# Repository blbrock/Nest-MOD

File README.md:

# Nest-MOD
Nest-MOD is a hardware and software interface to allow Nest Thermostats to work more efficiently with high efficiency
modulating/condensing boilers and furnaces that incorporate outdoor reset.

Requires python_nest API developed by Jason Kölker:
https://github.com/jkoelker/python-nest/

# Background
Modulating/Condensing (mod/con) boilers with Outdoor Reset (ODR) function are among the most energy 
efficient home heating devices available. However, because mod/con boilers operate at lower output 
temperatures than conventional boilers and furnaces, they do not work well with advanced programable 
and learning thermostats (e.g. Nest) that offer energy savings by programming nightly temperature 
setbacks or when homes are not occupied. Mod/con boilers with ODR adjust their heat output to compensate 
for outdoor temperatures by dialing back heat ouput during warm weather and increasing output when it is 
cold. A properly tuned mod/con ODR boiler will produce just enough heat to compensate for the building's 
heat loss and therefore run at lower temperatures for periods of time compared to a conventional system.

Because of their lower operating temperatures, mod/con ODR boilers can take many hours to recover from a 
temperature setback, if they recover at all. This is particularly true for radiant floor heating systems 
which are great for maintaining temperatures, but respond slowly to thermostat changes. 
Some boilers include a boost function that increases boiler output to speed recovery from temperature 
setbacks but many do not. 

Using temperature setbacks with radiant floor heating, and particularly with mod/con boilers, is a 
controversial topic. However, a study conducted by the National Renewable Energy Laboratory (NREL) 
indicates that nightly temperature setbacks do save energy in radiant floor, mod/con systems even if the 
boiler has to work harder to recover from those setbacks (http://www.nrel.gov/docs/fy14osti/60200.pdf).

Most networked thermostats do not include support for ODR furnaces and boilers. Nest 3rd 
generation thermostats sold in European markets now provides support for OpenTherm compliant modulating 
boilers which allows the thermostat to communicate with the boiler but currently cannot control boiler 
temperature. Based on discussions with Nest support, there doesn't appear to be any plan to implement 
modulating boiler support of any kind in the US. Therefore, one of the main energy saving advantages of 
programable thermostats is lost on systems that cannot recover from temperature setbacks in a reasonable 
time.

Frustrated by the lack of support for modulating boilers, I decided to build my own interface shield for 
a Raspberry pi. The shield and software are designed for a Munchkin boiler but should work (with appropriate 
modifcation) on any boiler that uses a thermistor to control the ODR curve. 

# Features: 

The software monitors thermostat data and initiates an ODR override cycle when > 1.25F temperature increase 
is called by any thermostat. Three stages of boost are provided depending on the differential between room 
ambient temperature and the target temperature the thermostat is trying to reach. Boost stage (and boiler 
temperature) increases with increasing differentials. Temperature differental threshold for each boost stage 
can be adjusted in the configuration (.secrets) file. Once the differential between target and room temperature 
reaches < 0.25F, ODR override is canceled and the boiler returns to its default ODR state.

The software tracks all thermostats in a Nest account and adjusts boost stages upward or downward according to 
the maximum boost level being requested by all thermostats in the account.

# Extras:

1. boost.py - a simple command line program to provide manual boost if needed. Manual boost cycles are logged (see below).

2. Automatic dehumidifier adjustment:
The software contains an optional routine to adjust the humidity setting for a selected thermostat according 
to outside temperature. This is useful for controlling an HRV or dehumidifier to maintain optimal indoor
humidity in cold climates. This feature does not require the pi to function.

3. Data logging:
Data from nest thermostats may optionally be logged to a file by setting options in the .secrets configuration file. 
This produces a comma delimited file containing data from thermostats and boost conditions. his feature does not require the pi to function.

4. Data Graphing:
When executed, plot_nest.py will produce a graph of data for the past week for all thermostats.  This program has only been tested in a Windows PC environment and may need additional software, configuration, or modifiction to work on other platforms.

# Error checking and logging: 

ODR override events and communication failures are logged to nest_odr.log. If the device loses connection with
the Nest server during an ODR override cycle, it will continue to recheck the connection at 1 minute intervals 
for 30 minutes. If a connection is not made within 30 minutes, the ODR override is aborted and the boiler is 
returned to its default state.

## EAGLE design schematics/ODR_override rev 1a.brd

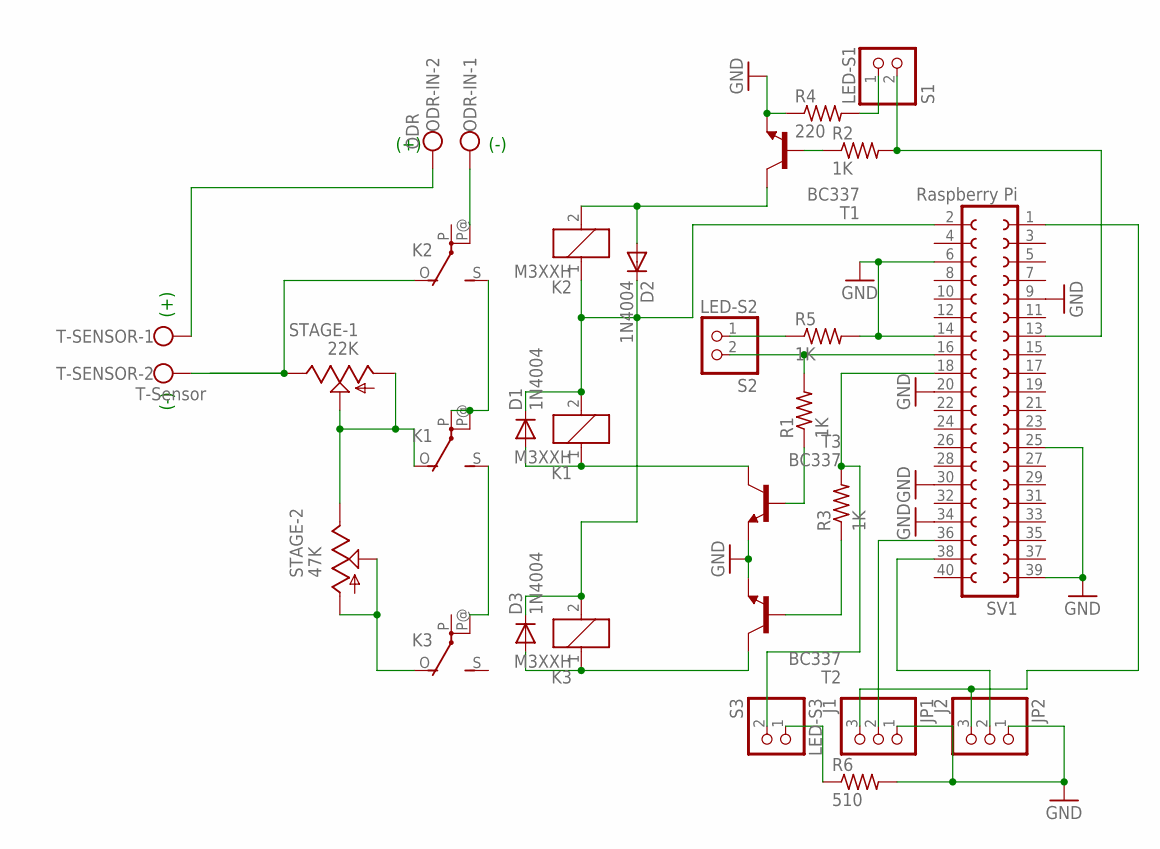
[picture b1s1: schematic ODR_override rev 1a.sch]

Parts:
D1, D2, D3: 1N4004; DO41-10
JP1: J1; 1X03
JP2: J2; 1X03
K1, K2, K3: M3XXH
LED-S1: S1; 1X02
LED-S2: S2; 1X02
LED-S3: S3; 1X02
ODR-IN: ODR; W237-102
R1, R2, R3, R5: 1K; 0204/7
R4: 220; 0204/7
R6: 510; 0204/7
STAGE-1: 22K; B25P
STAGE-2: 47K; B25P
SV1: Raspberry Pi; FE20-2
T1, T2, T3: BC337; TO92
T-SENSOR: T-Sensor; W237-102

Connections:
GND: JP1.1, JP2.1, R4.1, R5.2, R6.2, SV1.6, SV1.9, SV1.14, SV1.20, SV1.25, SV1.30, SV1.34, SV1.39, T1.1 (E), T2.1 (E), T3.1 (E)
unnamed: D1.A, K1.1, T3.3 (C)
unnamed: LED-S1.2, R2.2, SV1.13
unnamed: K1.S, K3.P@
unnamed: K2.P@, ODR-IN.1
unnamed: LED-S3.2, R3.2, SV1.18
unnamed: D3.A, K3.1, T2.3 (C)
unnamed: ODR-IN.2, T-SENSOR.1
unnamed: K1.O, STAGE-1.A, STAGE-1.S, STAGE-2.E
unnamed: D2.A, K2.2, T1.3 (C)
unnamed: R2.1, T1.2 (B)
unnamed: JP1.3, JP2.3, SV1.1
unnamed: LED-S2.2, R1.2, SV1.16
unnamed: R3.1, T2.2 (B)
unnamed: R1.1, T3.2 (B)
unnamed: K2.O, STAGE-1.E, T-SENSOR.2
unnamed: K1.P, K1.P@, K2.S
unnamed: K3.O, STAGE-2.A, STAGE-2.S
unnamed: JP1.2, SV1.36
unnamed: JP2.2, SV1.38
unnamed: LED-S1.1, R4.2
unnamed: LED-S2.1, R5.1
unnamed: LED-S3.1, R6.1
VCC: D1.C, D2.C, D3.C, K1.2, K2.1, K3.2, SV1.2

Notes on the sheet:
(+)
(-)

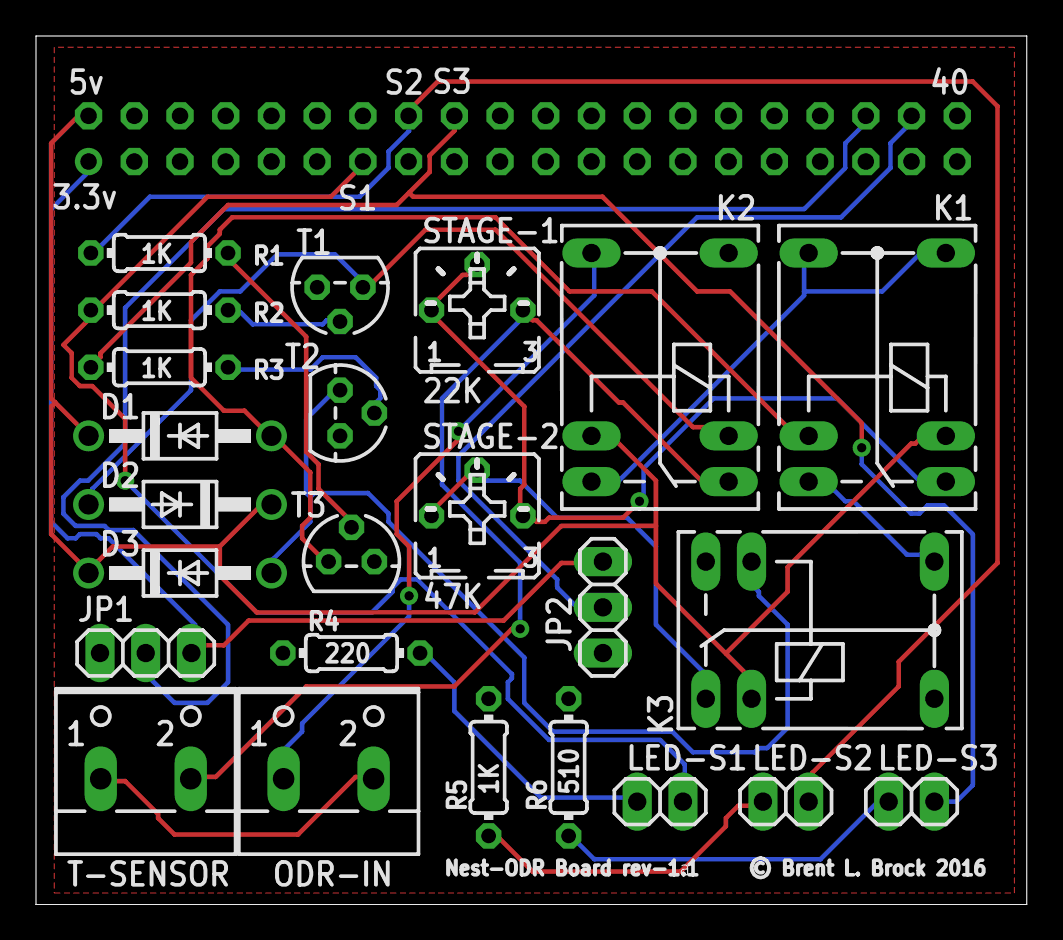
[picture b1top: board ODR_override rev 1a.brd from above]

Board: 2 copper layers, 55.0 x 48.2 mm, 25 parts (1 on the bottom side), 24 nets.

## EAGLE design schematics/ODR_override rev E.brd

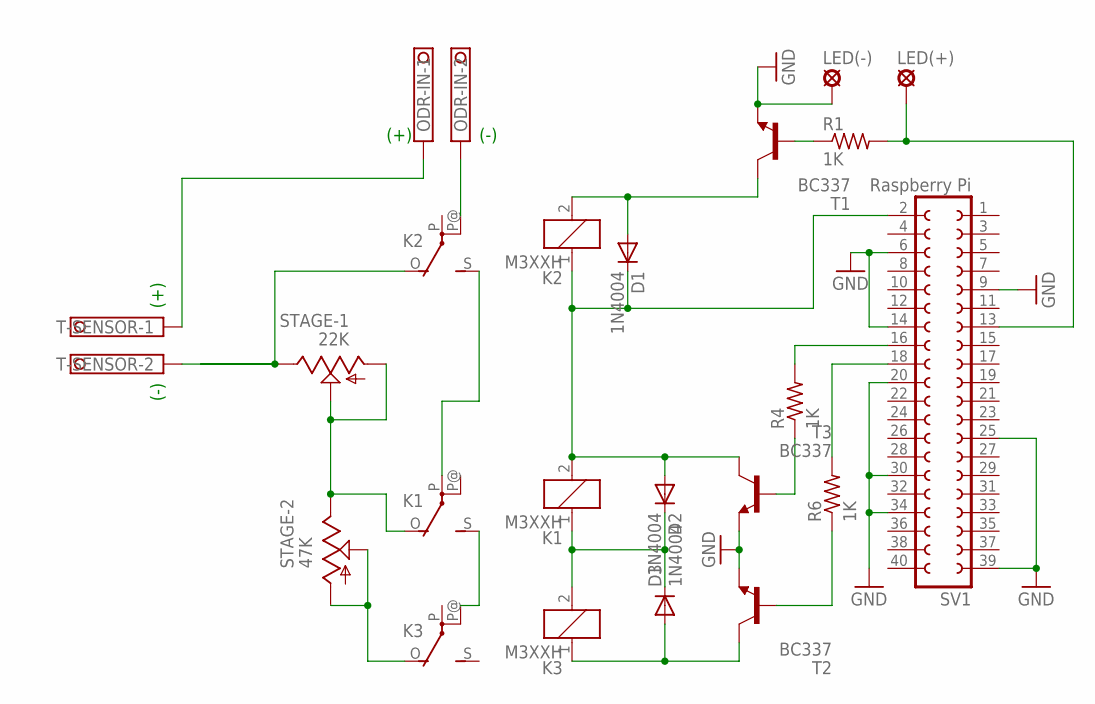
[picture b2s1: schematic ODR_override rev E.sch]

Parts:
D1, D2, D3: 1N4004; DO41-10
K1, K2, K3: M3XXH
LED(+): LSP11
LED(-): LSP11
ODR-IN: TERMINAL-BLOCK-3.5MM-2-PIN-ROUND-PAD; TERMINAL-BLOCK-2-PIN-3.5MM-ROUND-PAD
R1, R4, R6: 1K; 0204/5
STAGE-1: 22K; B25P
STAGE-2: 47K; B25P
SV1: Raspberry Pi; FE20-2
T1, T2, T3: BC337; TO92
T-SENSOR: TERMINAL-BLOCK-3.5MM-2-PIN-ROUND-PAD; TERMINAL-BLOCK-2-PIN-3.5MM-ROUND-PAD

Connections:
GND: LED(-).MP, SV1.6, SV1.9, SV1.14, SV1.20, SV1.25, SV1.30, SV1.34, SV1.39, T1.1 (E), T2.1 (E), T3.1 (E)
unnamed: LED(+).MP, R1.2, SV1.13
unnamed: R1.1, T1.2 (B)
unnamed: K1.S, K3.P@
unnamed: K2.P@, ODR-IN.2
unnamed: D1.C, D2.A, K1.2, K2.1, SV1.2, T3.3 (C)
unnamed: D3.A, K3.1, T2.3 (C)
unnamed: ODR-IN.1, T-SENSOR.1
unnamed: K1.O, STAGE-1.A, STAGE-1.S, STAGE-2.E
unnamed: D1.A, K2.2, T1.3 (C)
unnamed: R6.2, SV1.18
unnamed: D2.C, D3.C, K1.1, K3.2
unnamed: R4.2, SV1.16
unnamed: R6.1, T2.2 (B)
unnamed: R4.1, T3.2 (B)
unnamed: K2.O, STAGE-1.E, T-SENSOR.2
unnamed: K1.P, K2.S
unnamed: K3.O, STAGE-2.A, STAGE-2.S

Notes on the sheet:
(+)
(-)

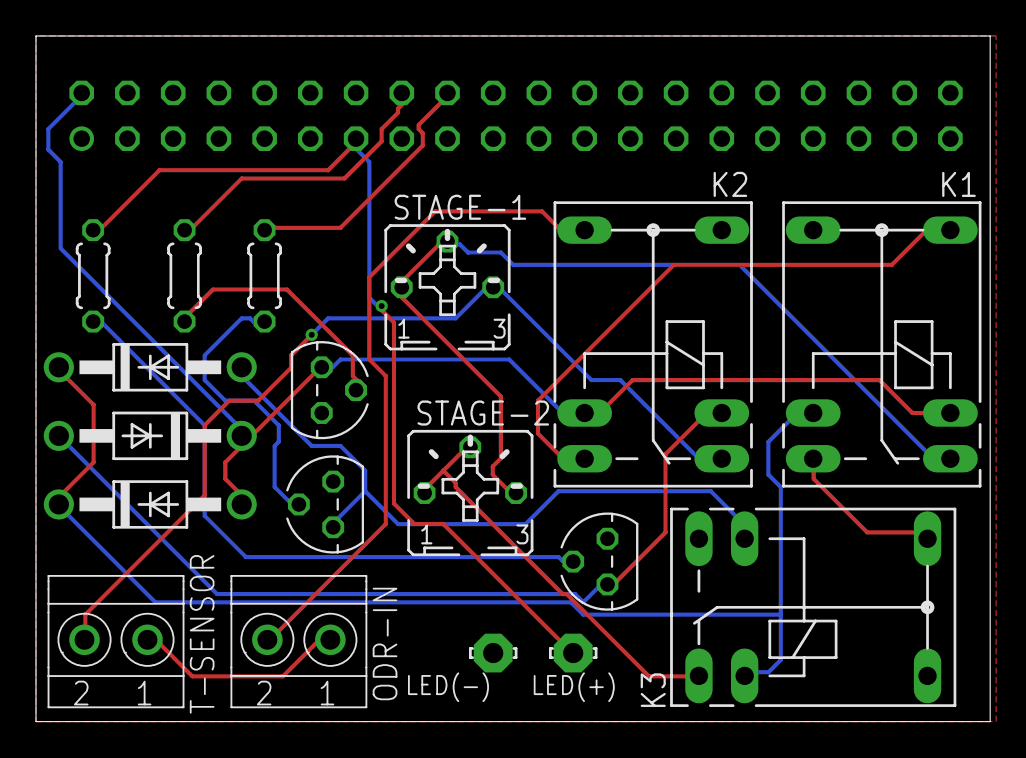
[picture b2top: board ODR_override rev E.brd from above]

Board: 2 copper layers, 53.0 x 38.1 mm, 19 parts (1 on the bottom side), 18 nets.

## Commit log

2016-01-16 schematics for Raspberry pi shield
    Provides GPIO interface to adjust boiler ODR. Designed for Raspberry pi
    A+ but should work with any model.
2016-01-16 generic config file
2016-01-16 add .gitignore
2016-01-16 readme update
2016-01-18 bug fixes
    fixed a bug in nest_odr.py that caused timing issues with failed
    connection warnings.
    Fixed errors in schematic relay wiring and updated schematic to include
    expansion jumpers.
2016-01-23 Bug fixes and enhancements
    Fixed a bug that spawned multiple threads which caused API connection to
    fail.
    Added routine to end boost cycle when thermostat no longer calling for
    heat.
2016-01-23 credential management
2016-01-23 update config file
2016-01-23 .gitignore
2016-01-24 feature enhancement
    added improved timer control to allow each thermostat to spawn or cancel
    boost increment threads as needed.
2016-01-24 bug fix
    Fixed bug causing individual boost cycles to report incorrect duration
    times
2016-01-26 improved stage control candidate
    creates a list of active (triggered) timers to track maximum requested
    boost levels for each calling thermostat. When a call for heat is
    satisfied on a thermostat, a reevaluation of stage level requests is
    triggered and the stage level is reset to the maximum level for all
    remaining active triggers.
2016-01-26 reporting enhancement
    did some housekeeping on log formatting
2016-01-26 remove log file
2016-01-29 enhancements
    - improved log reporting
    - added routine to check that GPIO states match program requests
    - moved target_humidity function to a separate module (nest_extras.py)
2016-01-30 logging enhancements
    Added option to write thermostat date to comma delimited log file.
2016-01-30 Update .secrets
    Added log_data parameter
    Changed default log_data and set_humidity to False
    Changed default staging time delays
2016-01-30 clearing reopository error
2016-01-30 configuration enhancement
    Added user defined log_dir to .secrets configuration file to allow
    custom location for storing log files.
2016-01-30 recommit
2016-01-30 Fixing repository
    .secrets is getting synced and shouldn't be.
2016-01-30 Rename .secrets_sample.txt to .secrets
    creating generic configuration file
2016-01-30 .gitignore
    can't get it to ignore .secrets file
2016-01-30 Rename .secrets to .secrets.example
2016-01-30 delete
2016-01-30 .secrets.example
    apparently it is not possible to keep different copies of a file in
    remote and local repositories even if they are ignored.
2016-01-31 code repair
    cleaned up damaged caused by botched commit
2016-02-22 1.1.0.0
    Complete rework of temperature increment routines. Dropped using timers
    to increment boiler temperature up as time boost time increased. Now
    sets boost levels based on temperature differentials between ambient
    room temperature and target temperature. Higher differentials initiate
    higher boiler temperatures. The boost curve now starts high and reduces
    boiler temps as ambient temp approaches target. This reduces problems
2016-02-22 updated .secrets
2016-02-22 add images
2016-02-22 image update
2016-02-22 convert images
2016-02-22 Create gh-pages branch via GitHub
2016-11-02 Misc tweaks and updates
2016-11-02 Dehumidifier modifications
    - Fixed bug preventing code from setting dehumidify setpoint
    - added max_hum parameter to set a maximum humidity setpoint
    - changed code to set humidity target on all thermostats to address
    problem with changes in device order in the structure causing wrong
    thermostat to get updated.
2016-11-02 update .secrets.example file
2016-11-03 Update schedule rooting for plotting data
    Program now extracts scheduled setpoints for plotting data directly from
    Nest API rather than from user-defined schedule dictionary.
2016-11-03 plot_nest.py
    added data plotting to software package
2016-11-22 Bug fixes and code enhancements
    - Fixed bug causing nest_odr to crash when logging data with schedule
    setpoints.
    - Removed redundancy of get_napi function. Function is now only in
    nest_extras.py.
    - Misc. code cleanup.
2016-11-23 Enhancement
    Updated get_napi() to print error returned by Nest API when data request
    fails.
2016-11-23 Bug fix
    - Changed default delay_rchk value in .secrets to 60 to avoid getting
    too many requests error from Nest API during boost cycle.
    - Reverted sleep value in nest_odr.py, check_connection() to 60.
2016-11-23 Bug fix
    fixed ommission of data-log() from import list

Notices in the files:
schematics/ODR_override rev 1a.brd:
© Brent L. Brock 2016
